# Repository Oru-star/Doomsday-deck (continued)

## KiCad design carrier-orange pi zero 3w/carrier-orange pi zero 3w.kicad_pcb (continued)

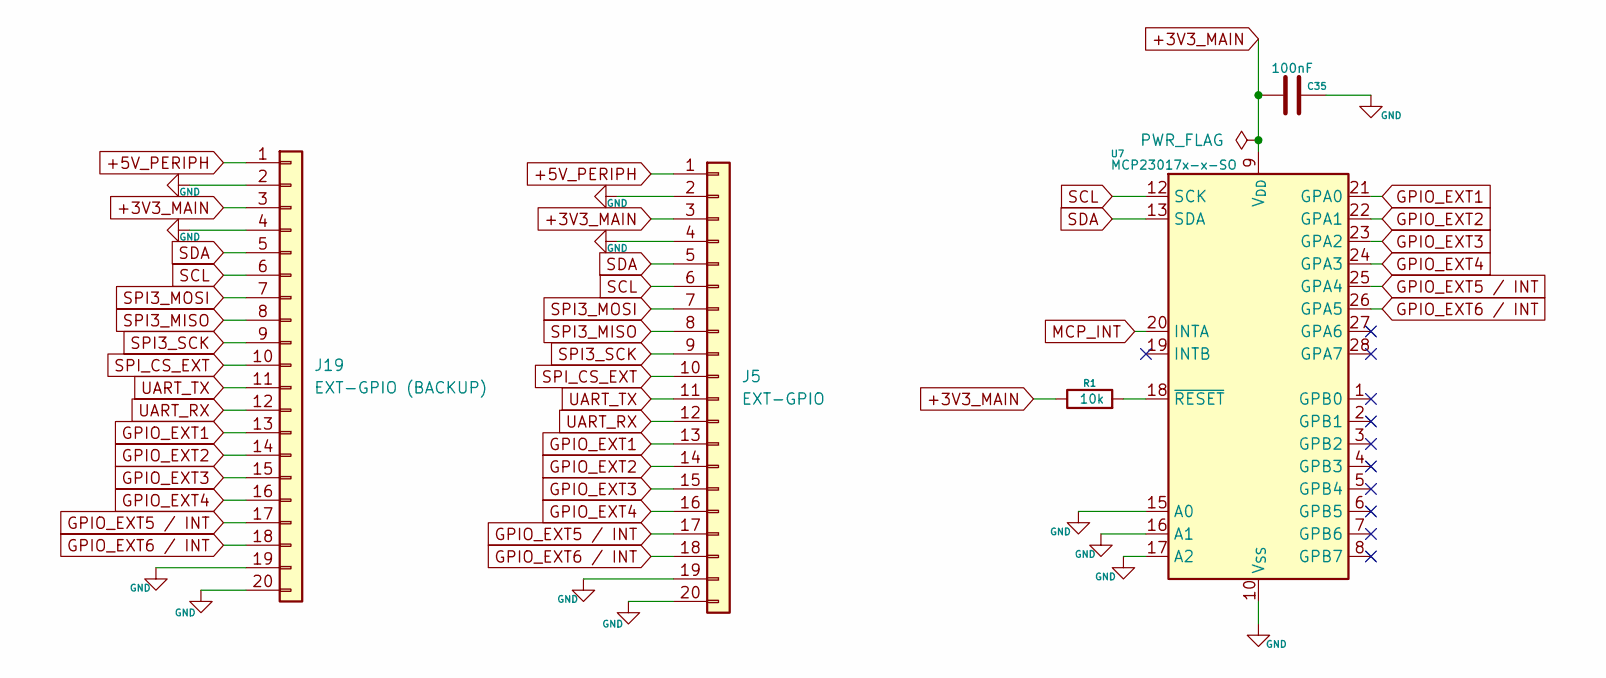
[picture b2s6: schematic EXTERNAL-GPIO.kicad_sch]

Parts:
C35: 100nF; C_0805_2012Metric
J5: EXT-GPIO; TE_2-84952-0_1x20-1MP_P1.0mm_Horizontal
J19: EXT-GPIO (BACKUP); PinHeader_2x10_P2.54mm_Vertical
R1: 10k; R_0805_2012Metric
U7: MCP23017x-x-SO; SOIC-28W_7.5x17.9mm_P1.27mm

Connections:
+3V3_MAIN: C35.1, J5.3, J19.3, R1.1, U7.9 (V_{DD}); also elsewhere on the board
+5V_PERIPH: J5.1, J19.1; also elsewhere on the board
GND: C35.2, J5.2, J5.4, J5.19, J5.20, J19.2, J19.4, J19.19, J19.20, U7.10 (V_{SS}), U7.15 (A0), U7.16 (A1), U7.17 (A2); also elsewhere on the board
GPIO_EXT1: J5.13, J19.13, U7.21 (GPA0)
GPIO_EXT2: J5.14, J19.14, U7.22 (GPA1)
GPIO_EXT3: J5.15, J19.15, U7.23 (GPA2)
GPIO_EXT4: J5.16, J19.16, U7.24 (GPA3)
GPIO_EXT5 / INT: J5.17, J19.17, U7.25 (GPA4)
GPIO_EXT6 / INT: J5.18, J19.18, U7.26 (GPA5)
MCP_INT: U7.20 (INTA); also elsewhere on the board
unnamed: R1.2, U7.18 (~RESET)
SCL: J5.6, J19.6, U7.12 (SCK); also elsewhere on the board
SDA: J5.5, J19.5, U7.13 (SDA); also elsewhere on the board
SPI3_MISO: J5.8, J19.8; also elsewhere on the board
SPI3_MOSI: J5.7, J19.7; also elsewhere on the board
SPI3_SCK: J5.9, J19.9; also elsewhere on the board
SPI_CS_EXT: J5.10, J19.10; also elsewhere on the board
UART_RX: J5.12, J19.12; also elsewhere on the board
UART_TX: J5.11, J19.11; also elsewhere on the board

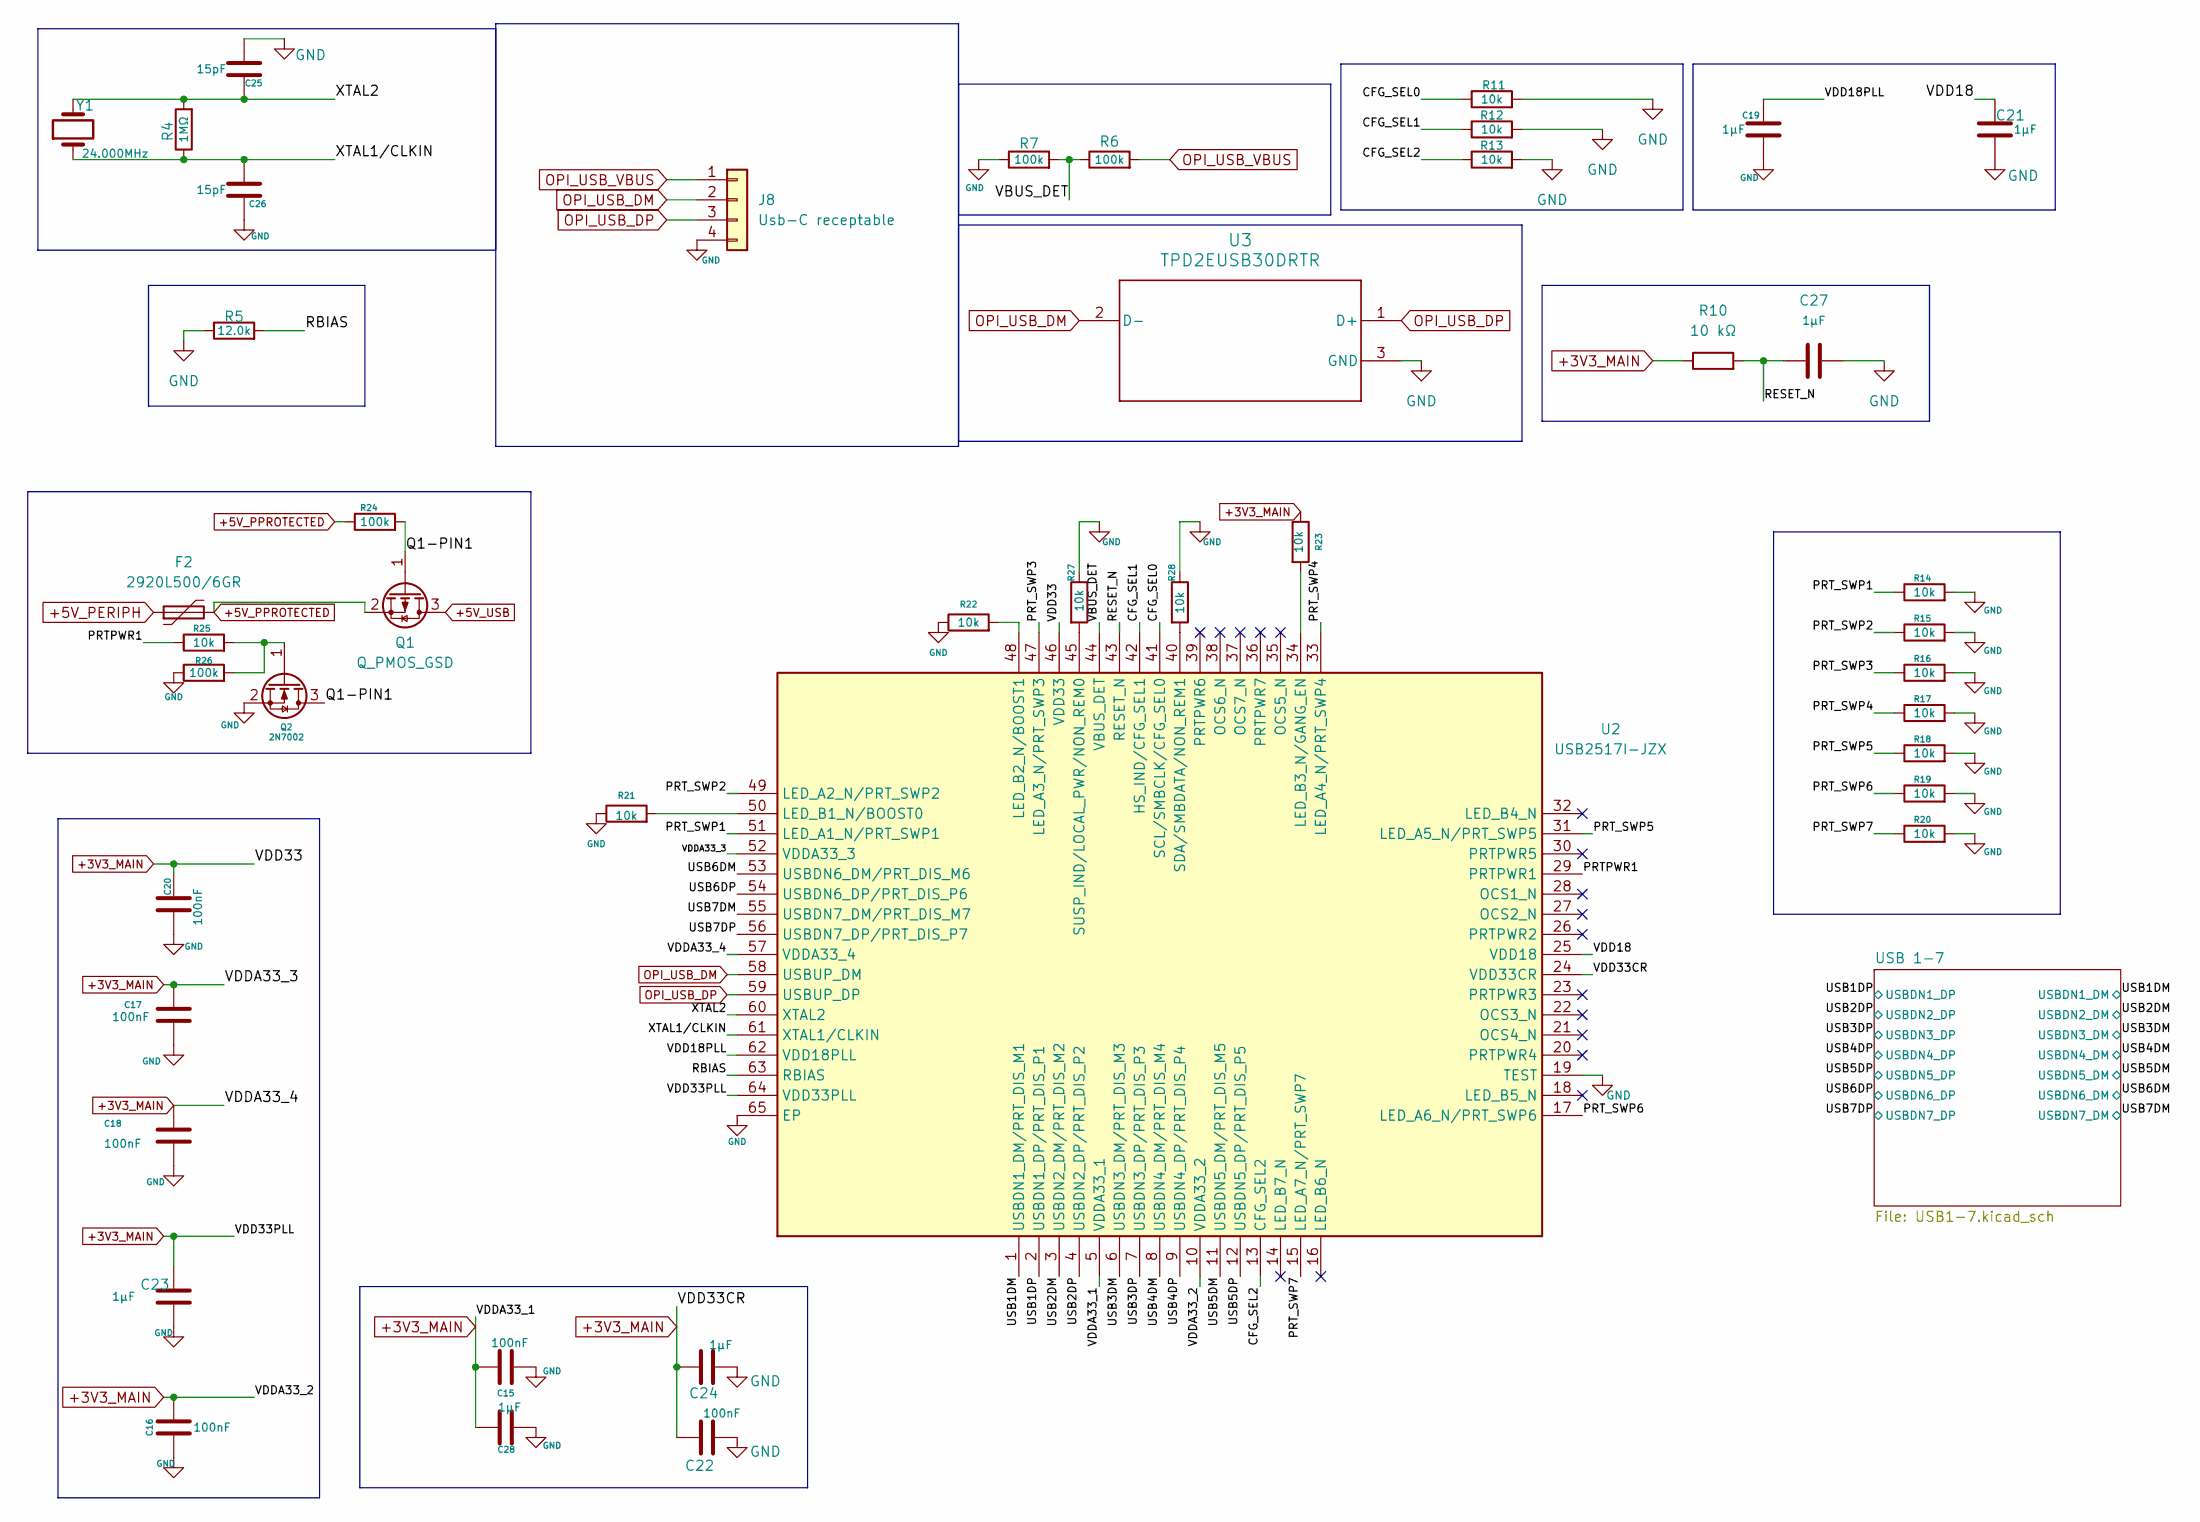
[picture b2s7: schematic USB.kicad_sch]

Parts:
C15, C16, C17, C18, C20, C22: 100nF; C_0805_2012Metric
C19, C21, C23, C24, C27, C28: 1µF; C_0805_2012Metric
C25, C26: 15pF; C_0805_2012Metric
F2: 2920L500/6GR; Fuse_2920_7451Metric
J8: Usb-C receptable; PinHeader_1x04_P2.54mm_Vertical
Q1: Q_PMOS_GSD; SOT-23
Q2: 2N7002; SOT-23
R4: 1MΩ; R_0805_2012Metric
R5: 12.0k; R_0805_2012Metric
R6, R7, R24, R26: 100k; R_0805_2012Metric
R10: 10 kΩ; R_0805_2012Metric
R11, R12, R13, R14, R15, R16, R17, R18, R19, R20, R21, R22, R23, R25, R27, R28: 10k; R_0805_2012Metric
U2: USB2517I-JZX; VQFN-64-1EP_9x9mm_P0.5mm_EP5.4x5.4mm_ThermalVias; Manufacturer_Part_Number USB2517I-JZX; Mouser Part Number 886-USB2517I-JZX
U3: TPD2EUSB30DRTR; SOT-723
Y1: 24.000MHz; Crystal_SMD_2016-4Pin_2.0x1.6mm

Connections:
+3V3_MAIN: C15.1, C16.1, C17.1, C18.1, C20.1, C22.1, C23.1, C24.1, C28.1, R10.1, R23.1, U2.5 (VDDA33_1), U2.10 (VDDA33_2), U2.24 (VDD33CR), U2.46 (VDD33), U2.52 (VDDA33_3), U2.57 (VDDA33_4), U2.64 (VDD33PLL); also elsewhere on the board
+5V_PERIPH: F2.1; also elsewhere on the board
+5V_PPROTECTED: F2.2, Q1.2 (S), R24.1
+5V_USB: Q1.3 (D); also elsewhere on the board
/USB/CFG_SEL0: R11.1, U2.41 (SCL/SMBCLK/CFG_SEL0)
/USB/CFG_SEL1: R12.1, U2.42 (HS_IND/CFG_SEL1)
/USB/CFG_SEL2: R13.1, U2.13 (CFG_SEL2)
/USB/PRTPWR1: R25.1, U2.29 (PRTPWR1)
/USB/PRT_SWP1: R14.1, U2.51 (LED_A1_N/PRT_SWP1)
/USB/PRT_SWP2: R15.1, U2.49 (LED_A2_N/PRT_SWP2)
/USB/PRT_SWP3: R16.1, U2.47 (LED_A3_N/PRT_SWP3)
/USB/PRT_SWP4: R17.1, U2.33 (LED_A4_N/PRT_SWP4)
/USB/PRT_SWP5: R18.1, U2.31 (LED_A5_N/PRT_SWP5)
/USB/PRT_SWP6: R19.1, U2.17 (LED_A6_N/PRT_SWP6)
/USB/PRT_SWP7: R20.1, U2.15 (LED_A7_N/PRT_SWP7)
/USB/Q1-PIN1: Q1.1 (G), Q2.3 (D), R24.2
/USB/RBIAS: R5.2, U2.63 (RBIAS)
/USB/RESET_N: C27.1, R10.2, U2.43 (RESET_N)
/USB/USB1DM: U2.1 (USBDN1_DM/PRT_DIS_M1); also elsewhere on the board
/USB/USB1DP: U2.2 (USBDN1_DP/PRT_DIS_P1); also elsewhere on the board
/USB/USB2DM: U2.3 (USBDN2_DM/PRT_DIS_M2); also elsewhere on the board
/USB/USB2DP: U2.4 (USBDN2_DP/PRT_DIS_P2); also elsewhere on the board
/USB/USB3DM: U2.6 (USBDN3_DM/PRT_DIS_M3); also elsewhere on the board
/USB/USB3DP: U2.7 (USBDN3_DP/PRT_DIS_P3); also elsewhere on the board
/USB/USB4DM: U2.8 (USBDN4_DM/PRT_DIS_M4); also elsewhere on the board
/USB/USB4DP: U2.9 (USBDN4_DP/PRT_DIS_P4); also elsewhere on the board
/USB/USB5DM: U2.11 (USBDN5_DM/PRT_DIS_M5); also elsewhere on the board
/USB/USB5DP: U2.12 (USBDN5_DP/PRT_DIS_P5); also elsewhere on the board
/USB/USB6DM: U2.53 (USBDN6_DM/PRT_DIS_M6); also elsewhere on the board
/USB/USB6DP: U2.54 (USBDN6_DP/PRT_DIS_P6); also elsewhere on the board
/USB/USB7DM: U2.55 (USBDN7_DM/PRT_DIS_M7); also elsewhere on the board
/USB/USB7DP: U2.56 (USBDN7_DP/PRT_DIS_P7); also elsewhere on the board
/USB/VBUS_DET: R6.1, R7.2, U2.44 (VBUS_DET)
/USB/VDD18: C21.1, U2.25 (VDD18)
/USB/VDD18PLL: C19.1, U2.62 (VDD18PLL)
/USB/XTAL1/CLKIN: C26.1, R4.1, U2.61 (XTAL1/CLKIN), Y1.1
/USB/XTAL2: C25.2, R4.2, U2.60 (XTAL2), Y1.2
GND: C15.2, C16.2, C17.2, C18.2, C19.2, C20.2, C21.2, C22.2, C23.2, C24.2, C25.1, C26.2, C27.2, C28.2, J8.4, Q2.2 (S), R5.1, R7.1, R11.2, R12.2, R13.2, R14.2, R15.2, R16.2, R17.2, R18.2, R19.2, R20.2, R21.1, R22.1, R26.1, R27.1, R28.1, U2.19 (TEST), U2.65 (EP), U3.3 (GND); also elsewhere on the board
unnamed: Q2.1 (G), R25.2, R26.2
unnamed: R21.2, U2.50 (LED_B1_N/BOOST0)
unnamed: R22.2, U2.48 (LED_B2_N/BOOST1)
unnamed: R23.2, U2.34 (LED_B3_N/GANG_EN)
unnamed: R28.2, U2.40 (SDA/SMBDATA/NON_REM1)
unnamed: R27.2, U2.45 (SUSP_IND/LOCAL_PWR/NON_REM0)
OPI_USB_DM: J8.2, U2.58 (USBUP_DM), U3.2 (D-)
OPI_USB_DP: J8.3, U2.59 (USBUP_DP), U3.1 (D+)
OPI_USB_VBUS: J8.1, R6.2

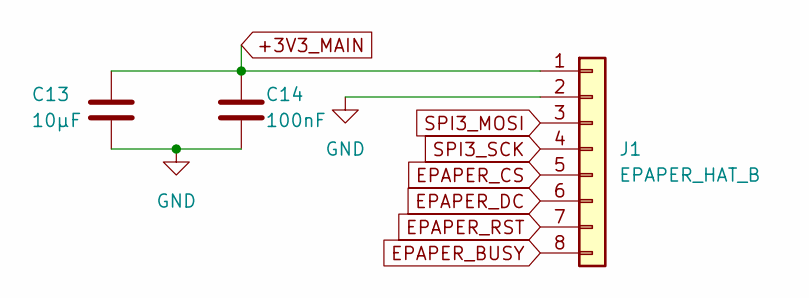
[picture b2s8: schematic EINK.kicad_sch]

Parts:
C13: 10µF; C_0805_2012Metric
C14: 100nF; C_0805_2012Metric
J1: EPAPER_HAT_B; PinHeader_1x08_P2.54mm_Vertical

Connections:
+3V3_MAIN: C13.1, C14.1, J1.1; also elsewhere on the board
EPAPER_BUSY: J1.8; also elsewhere on the board
EPAPER_CS: J1.5; also elsewhere on the board
EPAPER_DC: J1.6; also elsewhere on the board
EPAPER_RST: J1.7; also elsewhere on the board
GND: C13.2, C14.2, J1.2; also elsewhere on the board
SPI3_MOSI: J1.3; also elsewhere on the board
SPI3_SCK: J1.4; also elsewhere on the board

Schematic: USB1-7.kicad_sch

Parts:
J7: USB_A - 1; USB_A_Molex_48037-2200_Horizontal
J9: USB_A - 3; USB_A_Molex_48037-2200_Horizontal
J10: USB_A - 4; USB_A_Molex_48037-2200_Horizontal
J11: USB_A - 5; USB_A_Molex_48037-2200_Horizontal
J12: USB_A - 6 (For Display); PinHeader_1x04_P2.54mm_Vertical
J13: USB_A - 7 (For RTL SDR); PinHeader_1x04_P2.54mm_Vertical
J14: USB_A - 2 (Extra/For phone ); PinHeader_1x04_P2.54mm_Vertical

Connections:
+5V_PERIPH: J12.1 (VBUS); also elsewhere on the board
+5V_USB: J7.1 (VBUS), J9.1 (VBUS), J10.1 (VBUS), J11.1 (VBUS), J13.1 (VBUS), J14.1 (VBUS); also elsewhere on the board
/USB/USB1DM: J7.2 (D-); also elsewhere on the board
/USB/USB1DP: J7.3 (D+); also elsewhere on the board
/USB/USB2DM: J14.2 (D-); also elsewhere on the board
/USB/USB2DP: J14.3 (D+); also elsewhere on the board
/USB/USB3DM: J9.2 (D-); also elsewhere on the board
/USB/USB3DP: J9.3 (D+); also elsewhere on the board
/USB/USB4DM: J10.2 (D-); also elsewhere on the board
/USB/USB4DP: J10.3 (D+); also elsewhere on the board
/USB/USB5DM: J11.2 (D-); also elsewhere on the board
/USB/USB5DP: J11.3 (D+); also elsewhere on the board
/USB/USB6DM: J12.2 (D-); also elsewhere on the board
/USB/USB6DP: J12.3 (D+); also elsewhere on the board
/USB/USB7DM: J13.2 (D-); also elsewhere on the board
/USB/USB7DP: J13.3 (D+); also elsewhere on the board
GND: J7.4 (GND), J7.SH (Shield), J9.4 (GND), J9.SH (Shield), J10.4 (GND), J10.SH (Shield), J11.4 (GND), J11.SH (Shield), J12.4 (GND), J13.4 (GND), J14.4 (GND); also elsewhere on the board

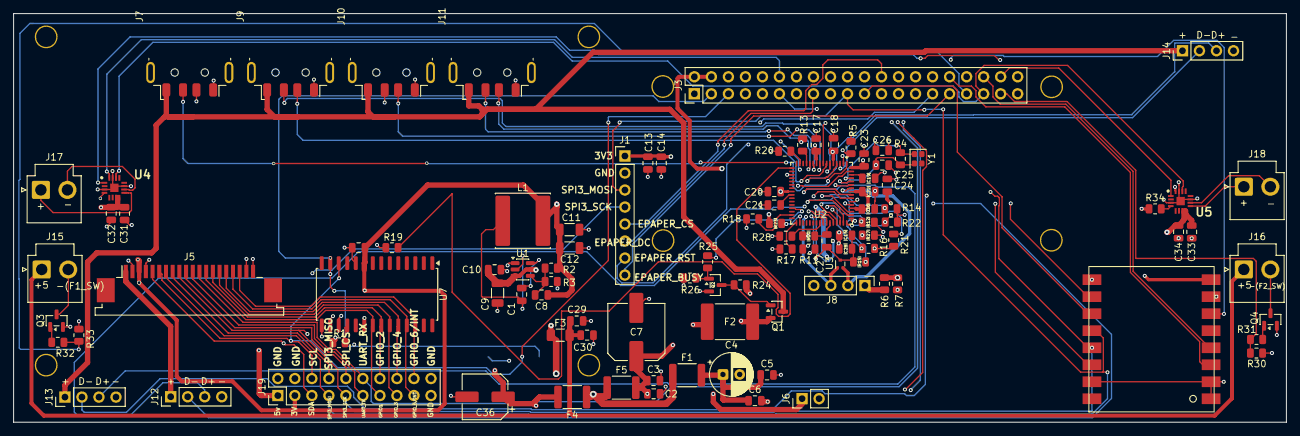
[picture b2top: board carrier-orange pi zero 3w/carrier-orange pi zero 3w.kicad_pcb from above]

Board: 4 copper layers, 190.0 x 61.0 mm, 103 parts (1 on the bottom side), 94 nets.

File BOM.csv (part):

Category,Reference(s),Part / item,Description / selected MPN,Qty required for build,Required unit,Purchase unit / pack,Pack size (pieces per purchase unit),Purchase quantity (units/packs),Listed price per purchase unit (INR),Purchase line total (INR),Allocated cost for required build qty (INR),Listed price per purchase unit (USD),Purchase line total (USD),Allocated cost (USD),Tax / price basis,Distributor,Product / datasheet link,Review status,Engineering / purchasing notes,Price basis,Count in displayed priced subtotal?,USD FX rate (INR per USD; dated 2026-10-10)
Compute,SBC1,Orange Pi Zero 3W 12GB,"Allwinner A733, 12GB LPDDR5, SKU PIB0GX6VVT15; product page says mini-HDMI 2.0 and Type-C DP Alt Mode; listing currently displays Sold out.",1,each,each,1,1,21680.00,21680.00,21680.00,224.02,224.02,224.02,Tax included; free shipping stated,Peach Imports,https://peachimports.com/products/orange-pi-zero-3w-12gb-lpd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,BLOCKER: listing currently sold out; pinout needs official confirmation,"Do not fabricate GPIO mapping using the name alone. Confirm board revision, exact 40-pin pinout, USB-C host/data role, cooling bundle and mechanical outline. Current PCB has an Orange Pi GPIO label but port alternate functions require official board documentation.",Product page captured 2026-10-11,"YES - reference price included for planning only; listing was sold out when checked, so this is not a currently orderable cost",96.7755
Display,DISP1,Waveshare 7HP-CAPQLED 7-inch display,"1024×600 QLED, capacitive touch; HDMI video + USB touch; 5V DC/USB power (external 5V/2A may be needed).",1,each,each,1,1,6639.00,6639.00,6639.00,68.60,68.60,68.60,GST included,Robu.in,https://robu.in/product/waveshare-7inch-1024x600-capacitive-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,Likely compatible; cables/power path missing,Orange Pi listing exposes Mini-HDMI 2.0 while the display uses HDMI: add a Mini-HDMI-to-HDMI cable. Touch needs a separate USB data connection. Verify 5V power input cable/connector and simultaneous load against UPS 5V/6A limit.,User screenshot; Waveshare product/wiki specifications,YES - listed price; tax basis as noted,96.7755
Keyboard,SW1-SW6,Kailh Choc V1 switches - selected Choc Yellow variant,"Neo Macro says 1 quantity = 10 switches; use 6, four spare. Choc V1 PCB footprint and stabilizer/keycap system differ from MX.",6,switches,10-switch pack,10,1,480.00,480.00,288.00,4.96,4.96,2.98,GST included; shipping at checkout,Neo Macro,https://neomacro.in/products/kailh-choc-v1-switches?variant=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,Compatible if PCB is designed for Choc V1; stock recheck,"Only six switch positions are covered. If the deck is still intended to have a full QWERTY keyboard, six switches/keycaps are insufficient; confirm final key count. Confirm selected colour/variant before checkout.",Current product page shows ₹480 and 1 qty=10 switches,YES - listed price; tax basis as noted,96.7755
Keyboard,KC1-KC6,Chocfox CFX Choc blank keycaps - 1U set,Selected frosted transparent white variant; listing price shown for a set/size option; screenshot selected 1U × 10 pcs.,6,keycaps,10-keycap pack,10,1,350.00,350.00,210.00,3.62,3.62,2.17,GST included; shipping at checkout,Neo Macro,https://neomacro.in/products/chocfox-cfx-choc-blank-keycaps?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,Likely compatible with Choc V1; verify exact variant pack,"One 10-piece pack covers six single-unit keys with four spare. Ensure these are the 1U Choc-compatible variant, not MX/keycaps or a different size option.",Current product page and user screenshot,YES - listed price; tax basis as noted,96.7755
Keyboard MCU,PICO-KB1,Raspberry Pi Pico 2,RP2350 microcontroller development board used as the keyboard controller; not Pico 2 W.,1,board,one development board,1,1,544.00,544.00,544.00,5.62,5.62,5.62,Robu product listing/category price ₹544 including GST; recheck availability and checkout price before order.,Robu.in,https://robu.in/product/raspberry-pi-pico-2/,ADDED - confirm intended keyboard MCU and physical mounting method,"The previous generated BOM did not include the Raspberry Pi Pico 2. Added because the project plan identifies Pico 2 as the keyboard PCB controller after replacing the earlier XIAO RP2040 choice. Confirm the keyboard PCB footprint and firmware target are for Pico 2 / RP2350, not Pico / RP2040 or Pico 2 W. Header/socket hardware for removable mounting is not included in this priced line and needs confirmation.",Robu listing displayed ₹544 on 2026-10-11; availability/checkout to be rechecked,"YES - price listed incl. GST, availability not confirmed at checkout",96.7755
Battery / power,BAT1-BAT4,Samsung INR21700-50S Li-ion cells,"21700, nominal 3.6V, 5000mAh, max charge 4.2V; UPS HAT E requires four 21700 flat-top cells in series.",4,each,each,1,4,519.00,2076.00,2076.00,5.36,21.45,21.45,GST included,Robu.in,https://robu.in/product/samsung-inr21700-50s-3-6v-5000mah-9c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,Electrical format appears suitable; confirm top style/physical fit,"Buy four matched cells from same model/batch; do not mix old/new or mismatched cells. Confirm flat-top construction and the UPS holder dimensions/orientation. Use the UPS charge/control system, not a separate unprotected charger.",User screenshot,YES - listed price; tax basis as noted,96.7755
Battery / power,UPS1,Waveshare UPS HAT (E),"4×21700 input, 5V output rated up to 6A, bidirectional USB-C charging, I²C monitoring, pogo-pad interface; batteries not included.",1,each,each,1,1,3866.77,3866.77,3866.77,39.96,39.96,39.96,Price shown excluding all taxes,Sharvi Electronics,https://sharvielectronics.com/product/ups-hat-e-for-raspberr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,POWER BUDGET BLOCKER / mechanical interface review,"Manufacturer specifies 5V/6A maximum and recommends respecting thermal limits. Verify pogo-pin coordinates, polarity, I²C and enclosure clearance; Waveshare advertises pogo compatibility for selected Raspberry Pi boards, not this Orange Pi carrier. Sum SBC + display + USB peripherals + two fans (0.4A) + audio/LoRa before relying on 6A.",User screenshot; official Waveshare UPS HAT E documentation,YES - listed price; tax basis as noted,96.7755
Secondary display,EINK1,Waveshare 2.13-inch 3-colour e-Paper HAT,"212×104 red/black/white, SPI, Raspberry Pi HAT form factor.",1,each,each,1,1,1178.82,1178.82,1178.82,12.18,12.18,12.18,GST included as shown,Zbotic,https://zbotic.in/product/waveshare-2-13inch-e-ink-paper-dis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,INTERFACE MISMATCH with shown 1×8 schematic connector,"The selected item is advertised as a Raspberry Pi e-Paper HAT; J1 on the schematic is an 8-pin SPI interface. Do not assume the HAT is just an 8-pin bare panel. Obtain the official pinout/mechanical drawing, then either map the HAT connector to the carrier correctly or select the bare display/interface version. Confirm physical clearance and connector pitch.",User screenshot; product listing,YES - listed price; tax basis as noted,96.7755
RF,RF1-RF2,"SMA male to U.FL/IPEX pigtail, 150mm","50Ω coaxial cable, SMA male ↔ U.FL/IPEX connector; listed DC to 6GHz.",2,cables,each,1,2,56.63,113.26,113.26,0.59,1.17,1.17,Price shown excluding all taxes,Sharvi Electronics,https://sharvielectronics.com/product/sma-male-connector-to-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,Quantity corrected to two per user list; destination/use of second pigtail still needs confirmation,Two SMA-male-to-U.FL/IPEX pigtails are specified by the user. One is for the Core1262 module RF connector if that module variant has the matching U.FL socket; confirm the second pigtail has a real endpoint before assembly. A pigtail is not an antenna. Add a 50Ω antenna matched to the selected module frequency and local rules.,User screenshot,YES - listed price; tax basis as noted,96.7755
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
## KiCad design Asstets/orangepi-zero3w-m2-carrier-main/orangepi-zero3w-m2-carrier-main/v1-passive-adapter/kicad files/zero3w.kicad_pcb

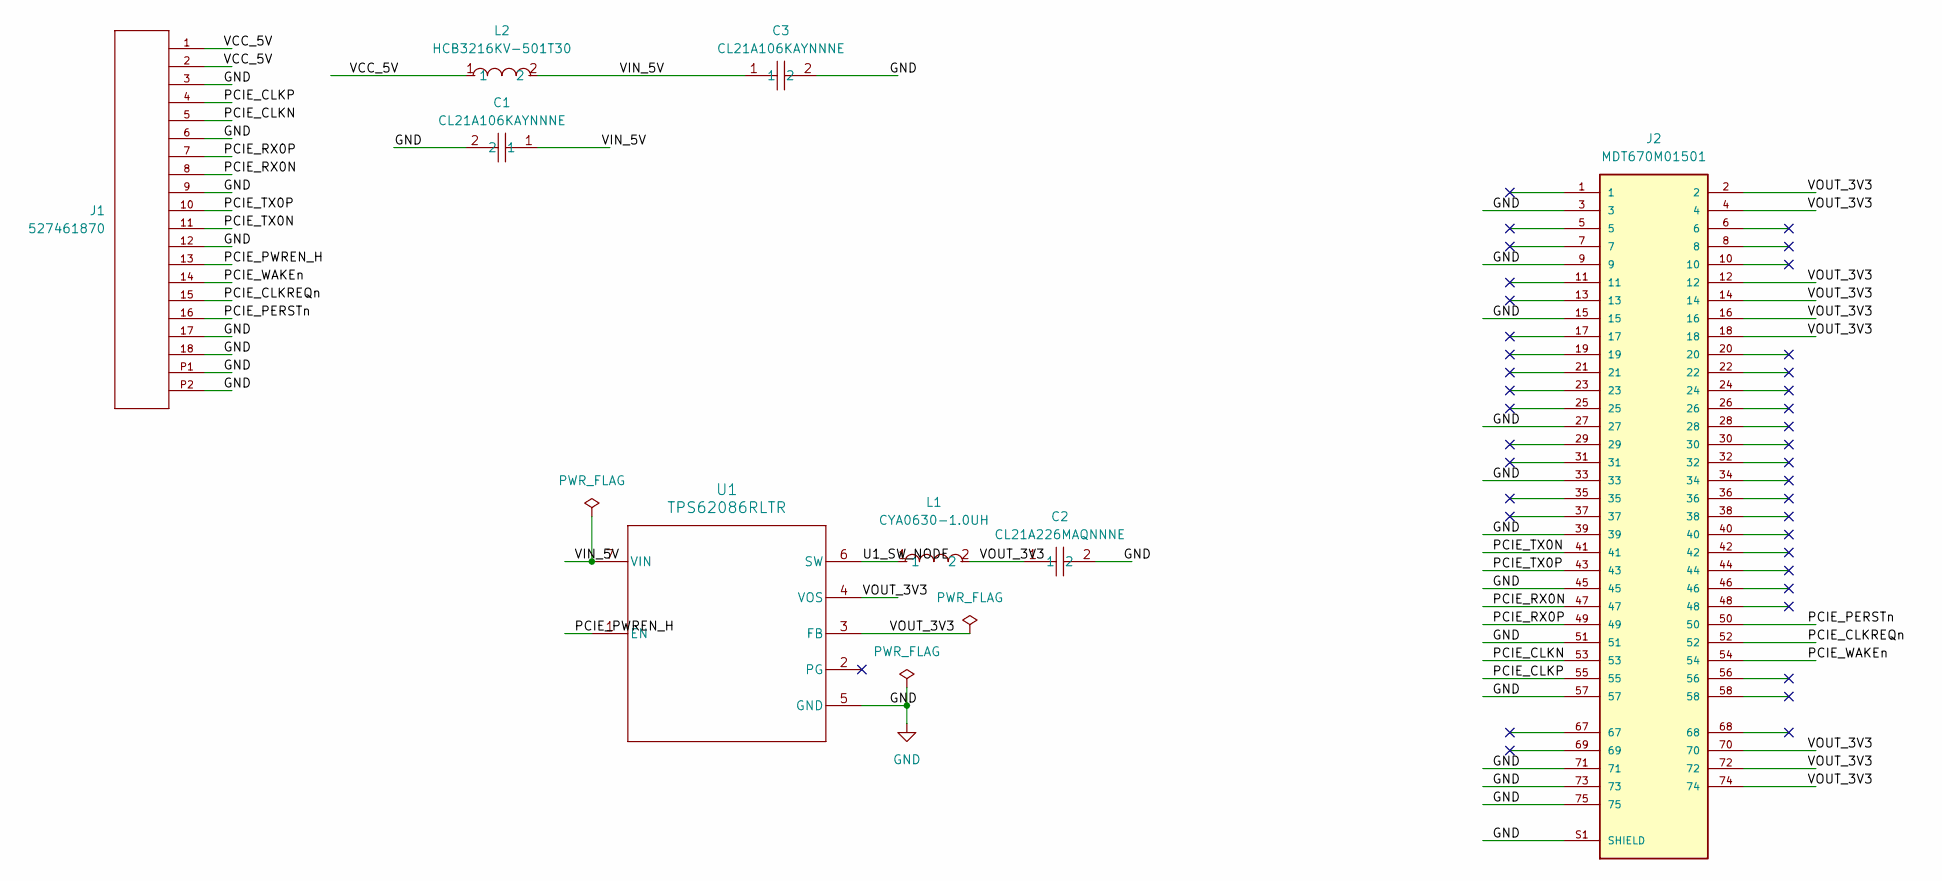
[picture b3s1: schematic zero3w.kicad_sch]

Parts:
C1, C3: CL21A106KAYNNNE; C0805; MPN CL21A106KAYNNNE; LCSC Part C15850
C2: CL21A226MAQNNNE; C0805; MPN CL21A226MAQNNNE; LCSC Part C45783
J1: 527461870; CON_527461870_MOL; MANUFACTURER_PART_NUMBER 527461870
J2: MDT670M01501; AMPHENOL_MDT670M01501; PARTREV 1
L1: CYA0630-1.0UH; IND-SMD_L7.2-W6.6_GPSR0730; MPN CYA0630-1.0UH; LCSC Part C5189744
L2: HCB3216KV-501T30; L1206; MPN HCB3216KV-501T30; LCSC Part C5139915
U1: TPS62086RLTR; RLT0007A

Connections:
/PCIE_CLKN: J1.5, J2.53
/PCIE_CLKP: J1.4, J2.55
/PCIE_CLKREQn: J1.15, J2.52
/PCIE_PERSTn: J1.16, J2.50
/PCIE_PWREN_H: J1.13, U1.1 (EN)
/PCIE_RX0N: J1.8, J2.47
/PCIE_RX0P: J1.7, J2.49
/PCIE_TX0N: J1.11, J2.41
/PCIE_TX0P: J1.10, J2.43
/PCIE_WAKEn: J1.14, J2.54
/U1_SW_NODE: L1.1, U1.6 (SW)
/VCC_5V: J1.1, J1.2, L2.1
/VIN_5V: C1.1, C3.1, L2.2, U1.7 (VIN)
/VOUT_3V3: C2.1, J2.2, J2.4, J2.12, J2.14, J2.16, J2.18, J2.70, J2.72, J2.74, L1.2, U1.3 (FB), U1.4 (VOS)
GND: C1.2, C2.2, C3.2, J1.3, J1.6, J1.9, J1.12, J1.17, J1.18, J1.P1, J1.P2, J2.3, J2.9, J2.15, J2.27, J2.33, J2.39, J2.45, J2.51, J2.57, J2.71, J2.73, J2.75, J2.S1 (SHIELD), J2.S2 (SHIELD), U1.5 (GND)

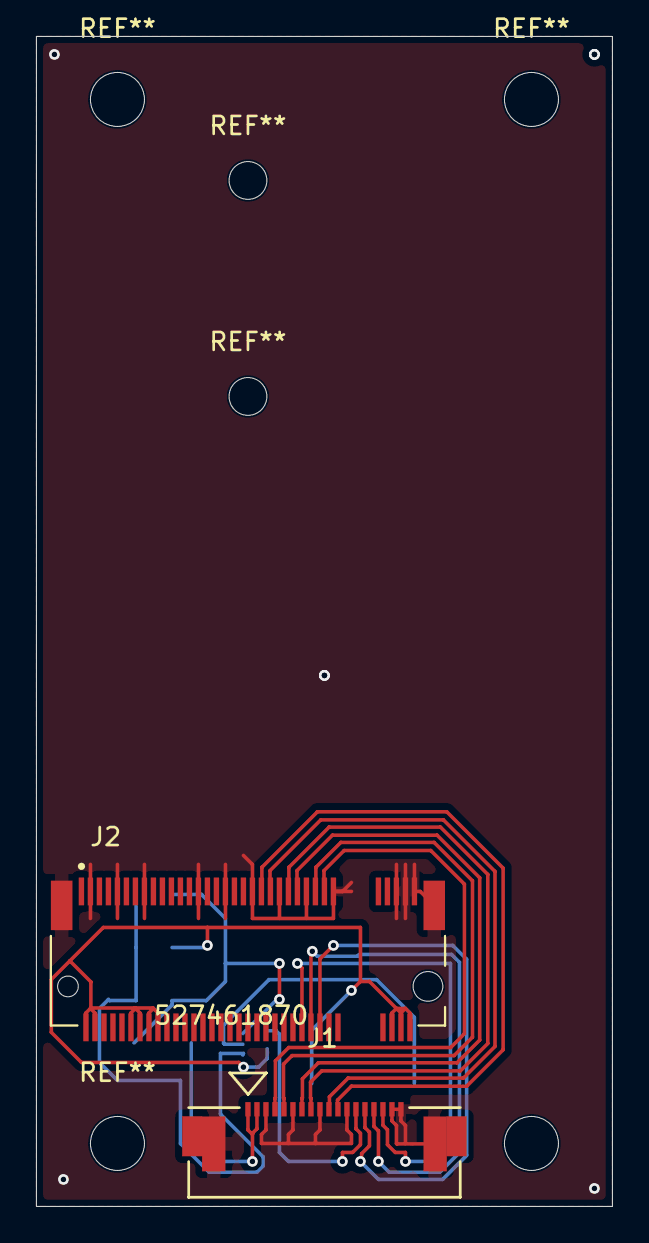
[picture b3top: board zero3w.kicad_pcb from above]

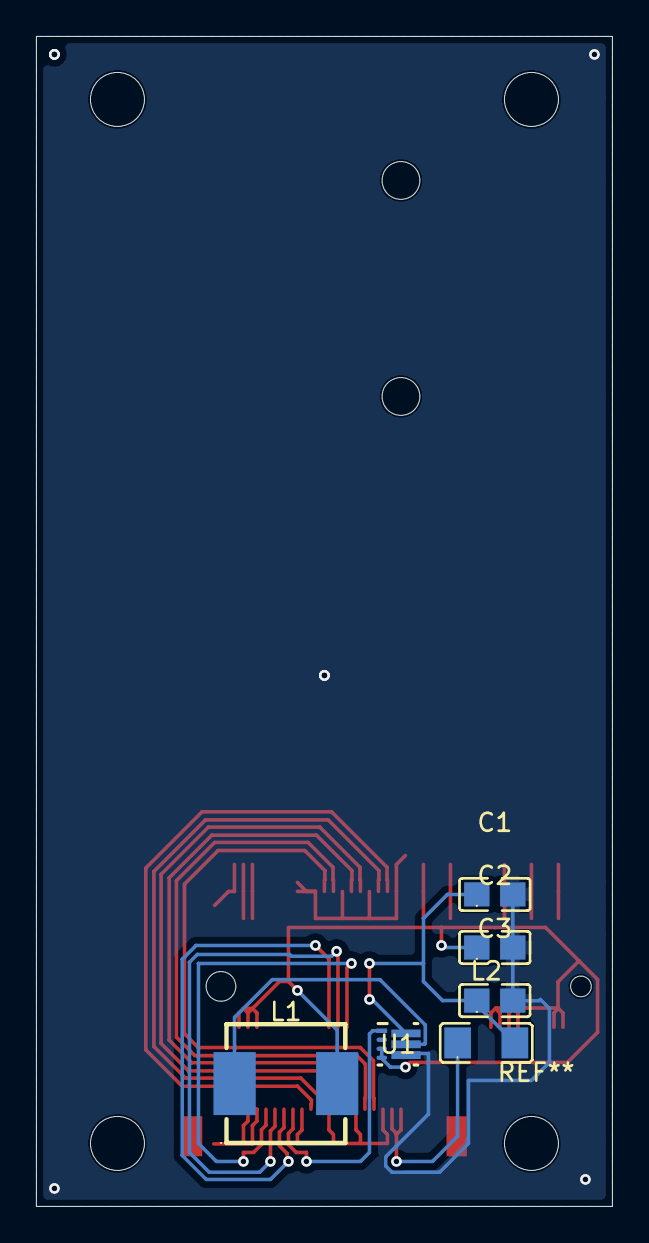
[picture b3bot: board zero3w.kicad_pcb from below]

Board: 2 copper layers, 32.0 x 65.0 mm, 8 parts (6 on the bottom side), 15 nets.

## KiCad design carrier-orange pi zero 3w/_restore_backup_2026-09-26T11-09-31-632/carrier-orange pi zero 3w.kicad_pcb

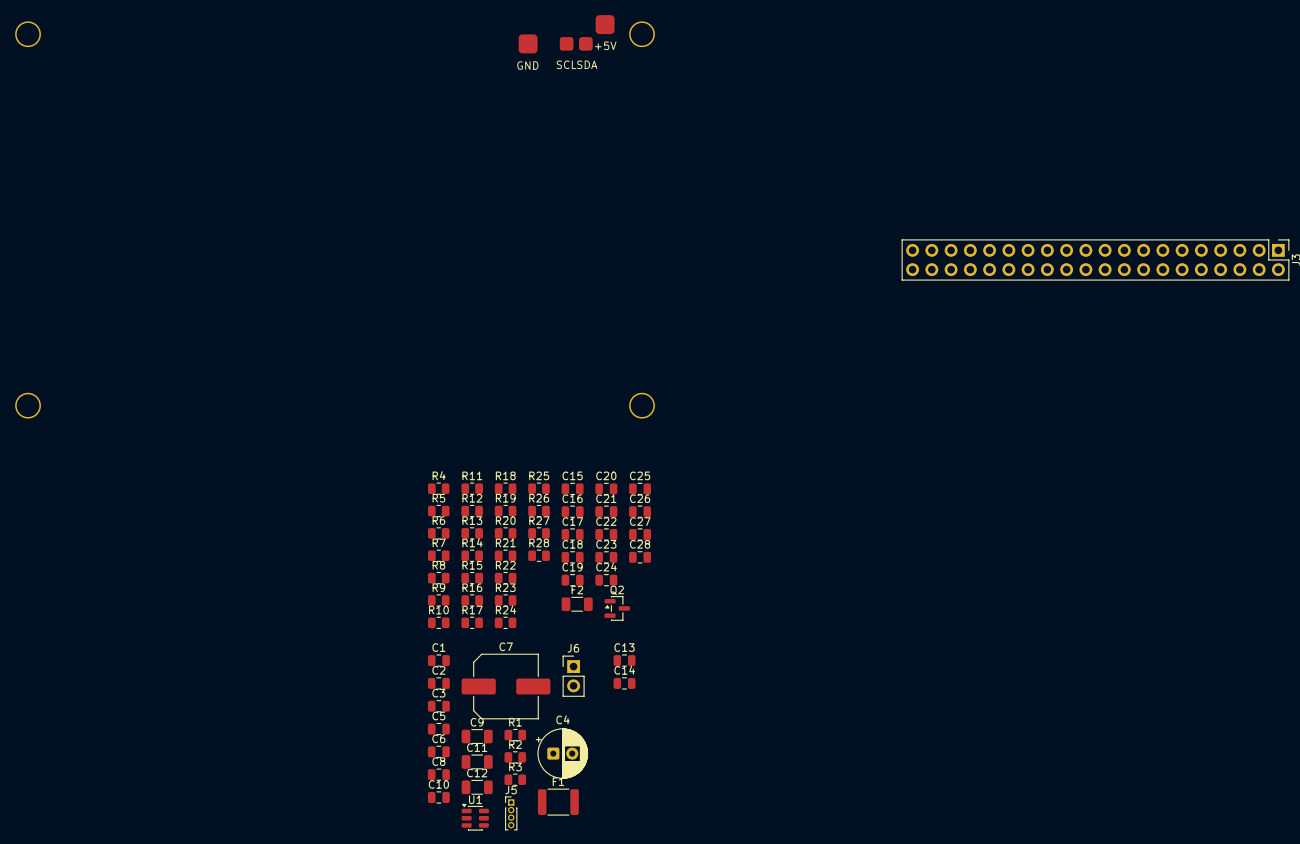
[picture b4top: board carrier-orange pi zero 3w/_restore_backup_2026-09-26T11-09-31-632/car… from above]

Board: 2 copper layers, 64 parts (0 on the bottom side), 17 nets, no tracks yet.

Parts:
C1, C3, C6, C10, C14, C15, C16, C17, C18, C20, C22, C23: 100nF; C_0805_2012Metric
C2, C19, C21, C24, C27, C28: 1µF; C_0805_2012Metric
C4: 100uF; CP_Radial_D6.3mm_P2.50mm
C5: 1uF; C_0805_2012Metric
C7: 470µF; C_Elec_8x10.2
C8: 47pF; C_0805_2012Metric
C9: 10µF; C_1206_3216Metric
C11, C12: 22µF; C_1206_3216Metric
C13: 10µF; C_0805_2012Metric
C25, C26: 33pF; C_0805_2012Metric
F1: 3A; Fuse_1812_4532Metric
F2: MF-R500; C_1206_3216Metric
J3: Orange Pi Zero 3W - 40-Pin GPIO; PinHeader_2x20_P2.54mm_Vertical
J4: Conn_01x04_Pin; UPS_HAT_E_Mating
J5: ORANGE_PI_POWER_CABLE; PinHeader_1x04_P1.00mm_Vertical
J6: 5V_PERIPHERALS; PinHeader_1x02_P2.54mm_Vertical
Q2: 2N7002; SOT-23
R1: 10K; R_0805_2012Metric
R2, R6, R7, R24, R26: 100k; R_0805_2012Metric
R3: 22.1k; R_0805_2012Metric
R4: 1M; R_0805_2012Metric
R5: 12.0k; R_0805_2012Metric
R8, R9: 5.1k; R_0805_2012Metric
R10: 10 kΩ; R_0805_2012Metric
R11, R12, R13, R14, R15, R16, R17, R18, R19, R20, R21, R22, R23, R25, R27, R28: 10k; R_0805_2012Metric
U1: TPS54302DDCT; SOT-23-6

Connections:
+3V3_MAIN: C8.1, C11.1, C12.1, C13.1, C14.1, C15.1, C16.1, C17.1, C18.1, C20.1, C22.1, C23.1, C24.1, C28.1, R2.1, R10.1, R23.1
+5V_MAIN: C2.1, C3.1, C7.1, C9.1, C10.1, F1.1, F2.1, J4.4, J6.1, U1.3 (VIN), U1.5 (EN)
+5V_OPI: C4.1, C5.1, C6.1, F1.2, J5.1, R1.2
+5V_PPROTECTED: F2.2, R24.1
/SCL: J3.5, J4.2
/SDA: J3.3, J4.3
/USB/Q1-PIN1: Q2.3 (D), R24.2
/USB/RESET_N: C27.1, R10.2
/USB/VBUS_DET: R6.1, R7.2
/USB/XTAL1/CLKIN: C26.1, R4.1
/USB/XTAL2: C25.2, R4.2
/power/CC: J5.3, R1.1
/power/FB: C8.2, R2.2, R3.1, U1.4 (FB)
GND: C2.2, C3.2, C4.2, C5.2, C6.2, C7.2, C9.2, C10.2, C11.2, C12.2, C13.2, C14.2, C15.2, C16.2, C17.2, C18.2, C19.2, C20.2, C21.2, C22.2, C23.2, C24.2, C25.1, C26.2, C27.2, C28.2, J4.1, J5.2, J6.2, Q2.2 (S), R3.2, R5.1, R7.1, R8.2, R9.2, R11.2, R12.2, R13.2, R14.2, R15.2, R16.2, R17.2, R18.2, R19.2, R20.2, R21.1, R22.1, R26.1, R27.1, R28.1, U1.1 (GND)
unnamed: Q2.1 (G), R25.2, R26.2
unnamed: C1.1, U1.6 (BOOT)
unnamed: C1.2, U1.2 (SW)
